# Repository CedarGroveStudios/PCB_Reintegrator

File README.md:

# The Reintegrator

### Convert Class-D audio signal to an unbalanced audio line level.

A mono Class-D audio to unbalanced audio line signal output converter. This version can act as a backpack for the Adafruit I2S 3watt audio amplifier.

[The Reintegrator board schematic](https://github.com/CedarGroveStudios/PCB_Reintegrator/blob/main/PCB/breakout.pdf)

OSH Park:
[https://oshpark.com/shared_projects/iI4kd3TW](https://oshpark.com/shared_projects/9TV0nn3f)

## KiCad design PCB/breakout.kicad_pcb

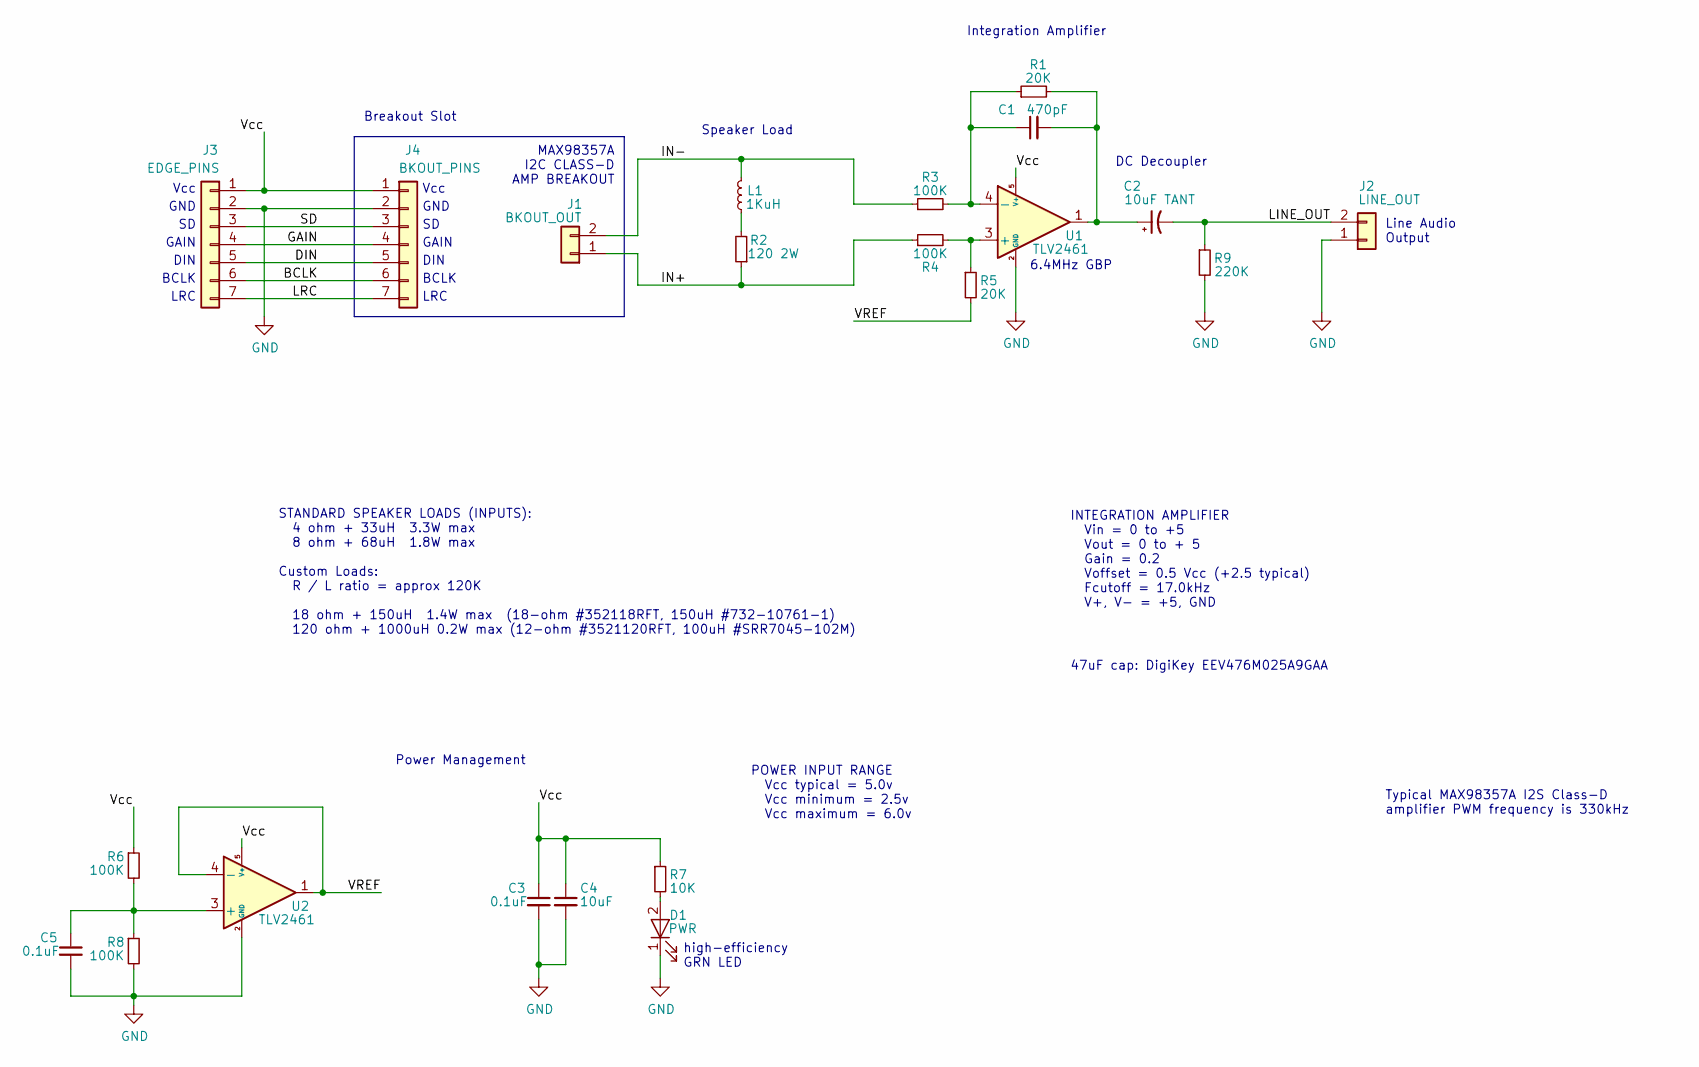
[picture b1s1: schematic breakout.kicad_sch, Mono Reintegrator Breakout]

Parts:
C1: 470pF; C_0805_2012Metric
C2: 10uF TANT; C_0805_2012Metric
C3, C5: 0.1uF; C_0805_2012Metric
C4: 10uF; C_0805_2012Metric
D1: PWR; LED_0805_2012Metric
J1: BKOUT_OUT; TerminalBlock_4Ucon_1x02_P3.50mm_Vertical
J2: LINE_OUT; PinSocket_1x02_P2.54mm_Vertical
J3: EDGE_PINS; PinSocket_1x07_P2.54mm_Vertical
J4: BKOUT_PINS; PinSocket_1x07_P2.54mm_Vertical
L1: 1KuH; L_Bourns_SRR7045
R1, R5: 20K; R_0805_2012Metric
R2: 120 2W; R_2512_6332Metric
R3, R4, R6, R8: 100K; R_0805_2012Metric
R7: 10K; R_0805_2012Metric
R9: 220K; R_0805_2012Metric
U1, U2: TLV2461; SOT-23-5

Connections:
/BCLK: J3.6, J4.6
/DIN: J3.5, J4.5
/GAIN: J3.4, J4.4
/IN+: J1.1, R2.1, R4.1
/IN-: J1.2, L1.2, R3.1
/LINE_OUT: C2.2, J2.2, R9.1
/LRC: J3.7, J4.7
/SD: J3.3, J4.3
/VREF: R5.2, U2.1, U2.4 (-)
/Vcc: C3.1, C4.1, J3.1, J4.1, R6.1, R7.1, U1.5 (V+), U2.5 (V+)
GND: C3.2, C4.2, C5.2, D1.1 (K), J2.1, J3.2, J4.2, R8.2, R9.2, U1.2 (GND), U2.2 (GND)
unnamed: C1.1, R1.1, R3.2, U1.4 (-)
unnamed: C1.2, C2.1, R1.2, U1.1
unnamed: C5.1, R6.2, R8.1, U2.3 (+)
unnamed: D1.2 (A), R7.2
unnamed: L1.1, R2.2
unnamed: R4.2, R5.1, U1.3 (+)

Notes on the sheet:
GND
high-efficiency GRN LED
LRC
Vcc
INTEGRATION AMPLIFIER Vin = 0 to +5 Vout = 0 to + 5 Gain = 0.2 Voffset = 0.5 Vcc (+2.5 typical) Fcutoff = 17.0kHz V+, V- = +5, GND
GAIN
STANDARD SPEAKER LOADS (INPUTS): 4 ohm + 33uH 3.3W max 8 ohm + 68uH 1.8W max Custom Loads: R / L ratio = approx 120K 18 ohm + 150uH 1.4W max (18-ohm #352118RFT, 150uH #732-10761-1) 120 ohm + 1000uH 0.2W max (12-ohm #3521120RFT, 100uH #SRR7045-102M)
BCLK
DIN
Line Audio Output
MAX98357A I2C CLASS-D AMP BREAKOUT
Integration Amplifier
DC Decoupler
Typical MAX98357A I2S Class-D amplifier PWM frequency is 330kHz
6.4MHz GBP
Power Management
POWER INPUT RANGE Vcc typical = 5.0v Vcc minimum = 2.5v Vcc maximum = 6.0v
47uF cap: DigiKey EEV476M025A9GAA
Breakout Slot
Speaker Load

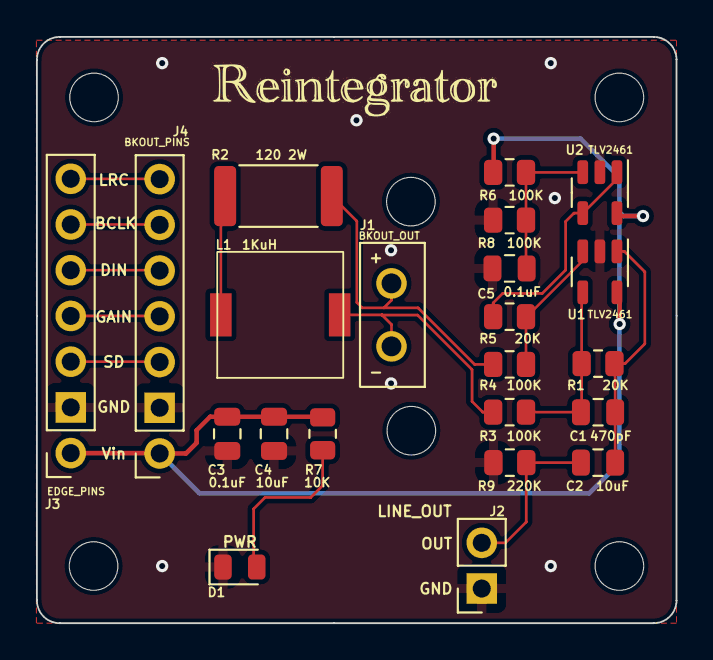
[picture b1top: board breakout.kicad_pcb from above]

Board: 2 copper layers, 35.5 x 32.6 mm, 22 parts (0 on the bottom side), 17 nets.

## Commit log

2023-05-31 initial repo load
2023-06-01 update kicad backups
